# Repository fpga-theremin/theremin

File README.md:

# FPGA based theremin

Open source digital FPGA based theremin project.

Hardware design and build instructions can be found on [FPGA Theremin Project Page](https://fpga-theremin.github.io/theremin/)

[Theremin](https://en.wikipedia.org/wiki/Theremin) is an electronic musical instrument controlled without physical contact by the thereminist (performer).
It is named after the Westernized name of its Soviet inventor, Léon Theremin (Лев Термéн), who patented the device in 1928. 

FPGA Theremin project is attempt to build modern digital theremin with rich set of features.

## License 
FPGA Theremin is open source hardware and software project.

All hardware designed for this project 
is published under [TAPR Open Hardware License](https://www.tapr.org/TAPR_Open_Hardware_License_v1.0.txt)

All software (including both HDL and C/C++ code) 
is published under [GNU GENERAL PUBLIC LICENSE Version 2](https://www.gnu.org/licenses/old-licenses/gpl-2.0.txt)

## HDL sources

Modules are written in SystemVerilog.

Some of modules use Xilinx Series 7 specific hardware blocks.

HLD code for modules:

* [theremin_sensor](https://github.com/fpga-theremin/theremin/tree/master/fpga/ip_repo/theremin_ip/src/theremin_sensor) - double channel high precision frequency meter
* [encoders_board](https://github.com/fpga-theremin/theremin/tree/master/fpga/ip_repo/theremin_ip/src/encoders_board) - interfacing to 5 incremental encoders with buttons and one tact button
* [lcd_controller](https://github.com/fpga-theremin/theremin/tree/master/fpga/ip_repo/theremin_ip/src/lcd_controller) - LCD controller with RGB interface and DMA
* [audio_io](https://github.com/fpga-theremin/theremin/tree/master/fpga/ip_repo/theremin_ip/src/audio_io) - audio out 2 * stereo * 24bit * 48KHz I2S outputs and one stereo * 24bit * 48KHz I2S input
* [theremin_i2c](https://github.com/fpga-theremin/theremin/tree/master/fpga/ip_repo/theremin_ip/src/theremin_i2c) - I2C support
* [theremin_io](https://github.com/fpga-theremin/theremin/tree/master/fpga/ip_repo/theremin_ip/src/theremin_io) - Top Level Module combining all theremin peripherials

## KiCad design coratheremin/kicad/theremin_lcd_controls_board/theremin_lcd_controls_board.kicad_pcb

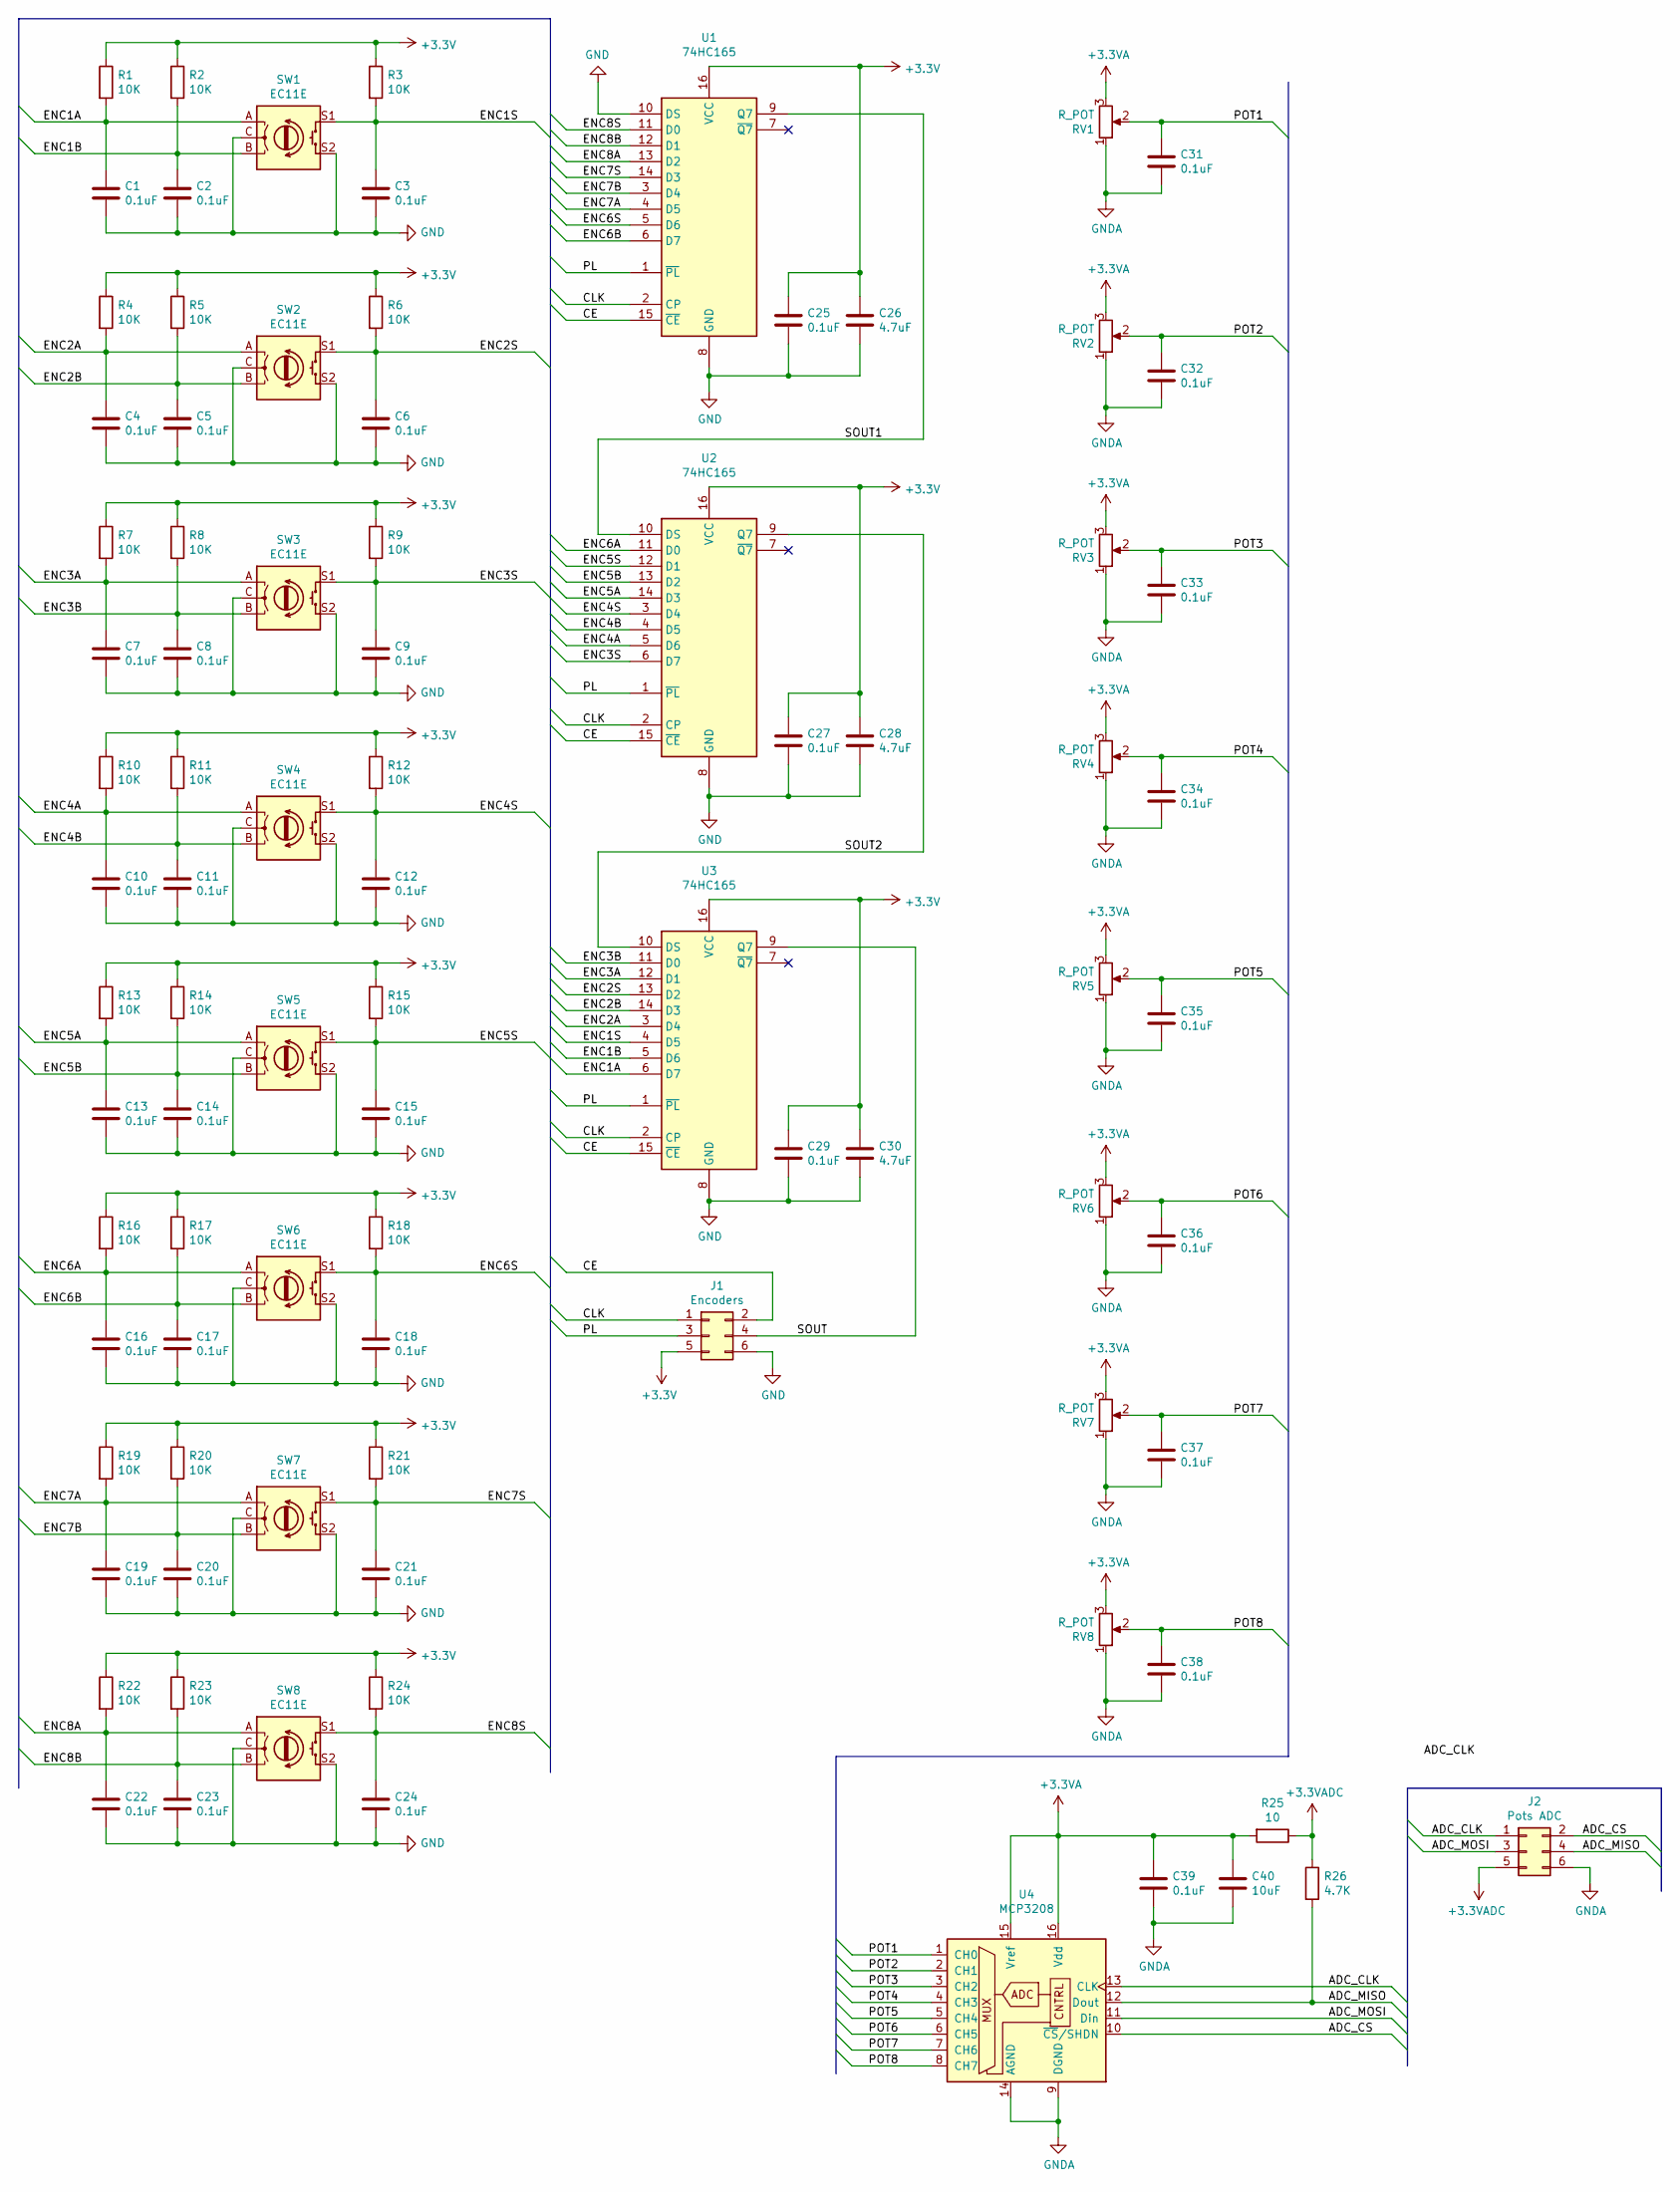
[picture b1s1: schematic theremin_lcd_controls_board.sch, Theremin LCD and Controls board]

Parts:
C1, C2, C3, C4, C5, C6, C7, C8, C9, C10, C11, C12, C13, C14, C15, C16, C17, C18, C19, C20, C21, C22, C23, C24, C25, C27, C29, C31, C32, C33, C34, C35, C36, C37, C38, C39: 0.1uF; C_0805_2012Metric
C26, C28, C30: 4.7uF; C_0805_2012Metric
C40: 10uF; C_0805_2012Metric
J1: Encoders; IDC-Header_2x03_P2.54mm_Vertical
J2: Pots ADC; IDC-Header_2x03_P2.54mm_Vertical
R1, R2, R3, R4, R5, R6, R7, R8, R9, R10, R11, R12, R13, R14, R15, R16, R17, R18, R19, R20, R21, R22, R23, R24: 10K; R_0805_2012Metric
R25: 10; R_0805_2012Metric
R26: 4.7K; R_0805_2012Metric
RV1, RV2, RV3, RV4, RV5, RV6, RV7, RV8: R_POT; Potentiometer_TT_P0915N
SW1, SW2, SW3, SW4, SW5, SW6, SW7, SW8: EC11E; RotaryEncoder_Alps_EC11E-Switch_Vertical_H20mm
U1, U2, U3: 74HC165; SO-16_3.9x9.9mm_P1.27mm
U4: MCP3208; SOIC-16_3.9x9.9mm_P1.27mm

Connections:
+3.3VA: C39.1, C40.1, R25.2, RV1.3, RV2.3, RV3.3, RV4.3, RV5.3, RV6.3, RV7.3, RV8.3, U4.15 (Vref), U4.16 (Vdd)
+3.3VADC: J2.5, R25.1, R26.1
+3V3: C25.1, C26.1, C27.1, C28.1, C29.1, C30.1, J1.5, R1.1, R2.1, R3.1, R4.1, R5.1, R6.1, R7.1, R8.1, R9.1, R10.1, R11.1, R12.1, R13.1, R14.1, R15.1, R16.1, R17.1, R18.1, R19.1, R20.1, R21.1, R22.1, R23.1, R24.1, U1.16 (VCC), U2.16 (VCC), U3.16 (VCC)
/ADC_CLK: J2.1, U4.13 (CLK)
/ADC_CS: J2.2, U4.10 (~CS~/SHDN)
/ADC_MISO: J2.4, R26.2, U4.12 (Dout)
/ADC_MOSI: J2.3, U4.11 (Din)
/CE: J1.2, U1.15 (~CE), U2.15 (~CE), U3.15 (~CE)
/CLK: J1.1, U1.2 (CP), U2.2 (CP), U3.2 (CP)
/ENC1A: C1.1, R1.2, SW1.A, U3.6 (D7)
/ENC1B: C2.1, R2.2, SW1.B, U3.5 (D6)
/ENC1S: C3.1, R3.2, SW1.S1, U3.4 (D5)
/ENC2A: C4.1, R4.2, SW2.A, U3.3 (D4)
/ENC2B: C5.1, R5.2, SW2.B, U3.14 (D3)
/ENC2S: C6.1, R6.2, SW2.S1, U3.13 (D2)
/ENC3A: C7.1, R7.2, SW3.A, U3.12 (D1)
/ENC3B: C8.1, R8.2, SW3.B, U3.11 (D0)
/ENC3S: C9.1, R9.2, SW3.S1, U2.6 (D7)
/ENC4A: C10.1, R10.2, SW4.A, U2.5 (D6)
/ENC4B: C11.1, R11.2, SW4.B, U2.4 (D5)
/ENC4S: C12.1, R12.2, SW4.S1, U2.3 (D4)
/ENC5A: C13.1, R13.2, SW5.A, U2.14 (D3)
/ENC5B: C14.1, R14.2, SW5.B, U2.13 (D2)
/ENC5S: C15.1, R15.2, SW5.S1, U2.12 (D1)
/ENC6A: C16.1, R16.2, SW6.A, U2.11 (D0)
/ENC6B: C17.1, R17.2, SW6.B, U1.6 (D7)
/ENC6S: C18.1, R18.2, SW6.S1, U1.5 (D6)
/ENC7A: C19.1, R19.2, SW7.A, U1.4 (D5)
/ENC7B: C20.1, R20.2, SW7.B, U1.3 (D4)
/ENC7S: C21.1, R21.2, SW7.S1, U1.14 (D3)
/ENC8A: C22.1, R22.2, SW8.A, U1.13 (D2)
/ENC8B: C23.1, R23.2, SW8.B, U1.12 (D1)
/ENC8S: C24.1, R24.2, SW8.S1, U1.11 (D0)
/PL: J1.3, U1.1 (~PL), U2.1 (~PL), U3.1 (~PL)
/POT1: C31.1, RV1.2, U4.1 (CH0)
/POT2: C32.1, RV2.2, U4.2 (CH1)
/POT3: C33.1, RV3.2, U4.3 (CH2)
/POT4: C34.1, RV4.2, U4.4 (CH3)
/POT5: C35.1, RV5.2, U4.5 (CH4)
/POT6: C36.1, RV6.2, U4.6 (CH5)
/POT7: C37.1, RV7.2, U4.7 (CH6)
/POT8: C38.1, RV8.2, U4.8 (CH7)
/SOUT: J1.4, U3.9 (Q7)
/SOUT1: U1.9 (Q7), U2.10 (DS)
/SOUT2: U2.9 (Q7), U3.10 (DS)
GND: C1.2, C2.2, C3.2, C4.2, C5.2, C6.2, C7.2, C8.2, C9.2, C10.2, C11.2, C12.2, C13.2, C14.2, C15.2, C16.2, C17.2, C18.2, C19.2, C20.2, C21.2, C22.2, C23.2, C24.2, C25.2, C26.2, C27.2, C28.2, C29.2, C30.2, J1.6, SW1.C, SW1.S2, SW2.C, SW2.S2, SW3.C, SW3.S2, SW4.C, SW4.S2, SW5.C, SW5.S2, SW6.C, SW6.S2, SW7.C, SW7.S2, SW8.C, SW8.S2, U1.8 (GND), U1.10 (DS), U2.8 (GND), U3.8 (GND)
GNDA: C31.2, C32.2, C33.2, C34.2, C35.2, C36.2, C37.2, C38.2, C39.2, C40.2, J2.6, RV1.1, RV2.1, RV3.1, RV4.1, RV5.1, RV6.1, RV7.1, RV8.1, U4.9 (DGND), U4.14 (AGND)

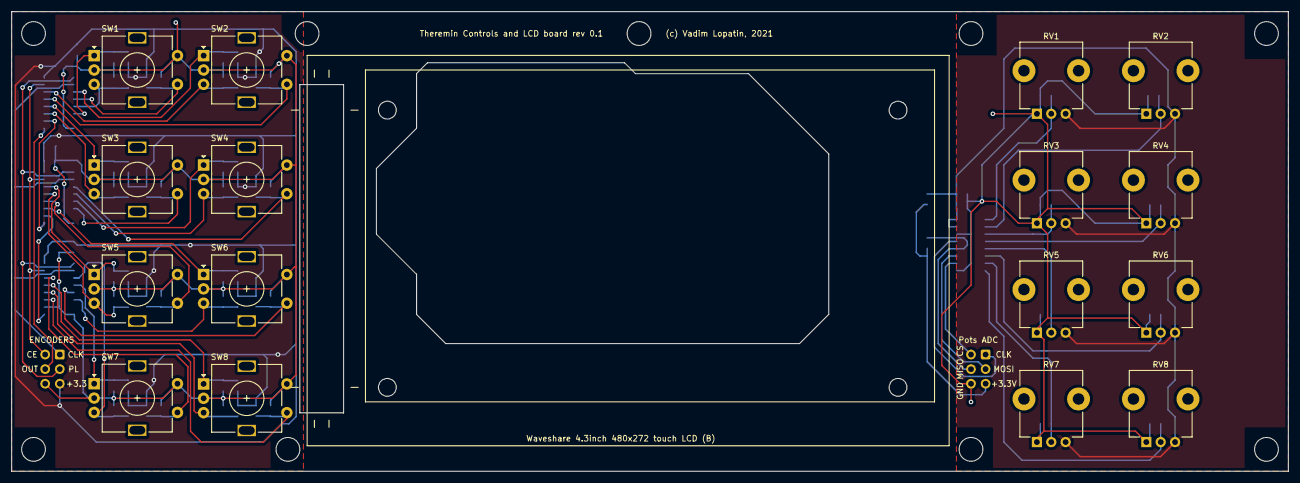
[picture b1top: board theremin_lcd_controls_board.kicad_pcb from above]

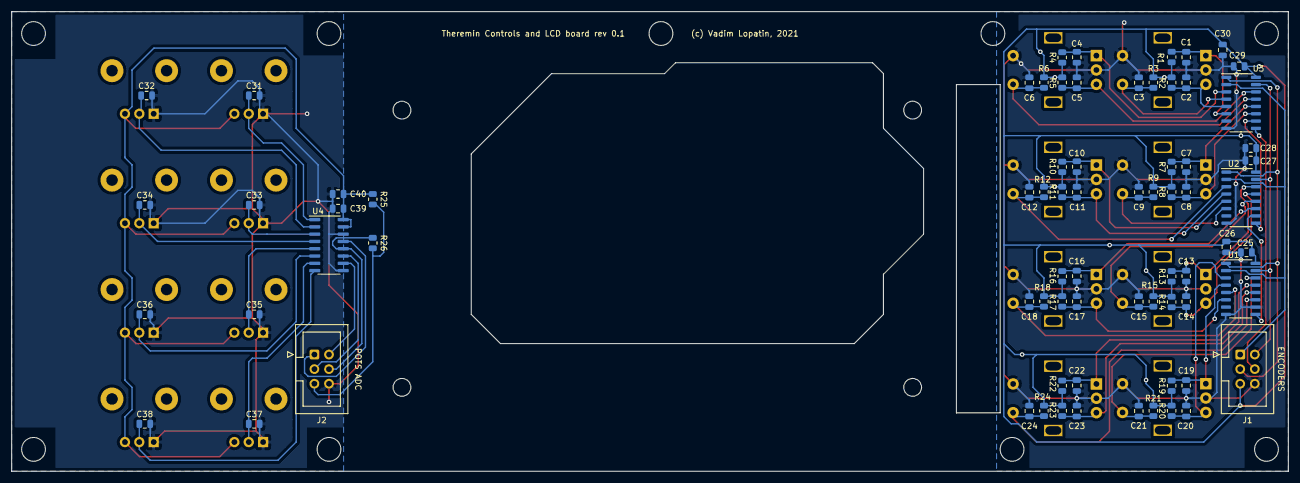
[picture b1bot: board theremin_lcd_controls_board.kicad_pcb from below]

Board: 2 copper layers, 222.2 x 80.0 mm, 88 parts (72 on the bottom side), 47 nets.

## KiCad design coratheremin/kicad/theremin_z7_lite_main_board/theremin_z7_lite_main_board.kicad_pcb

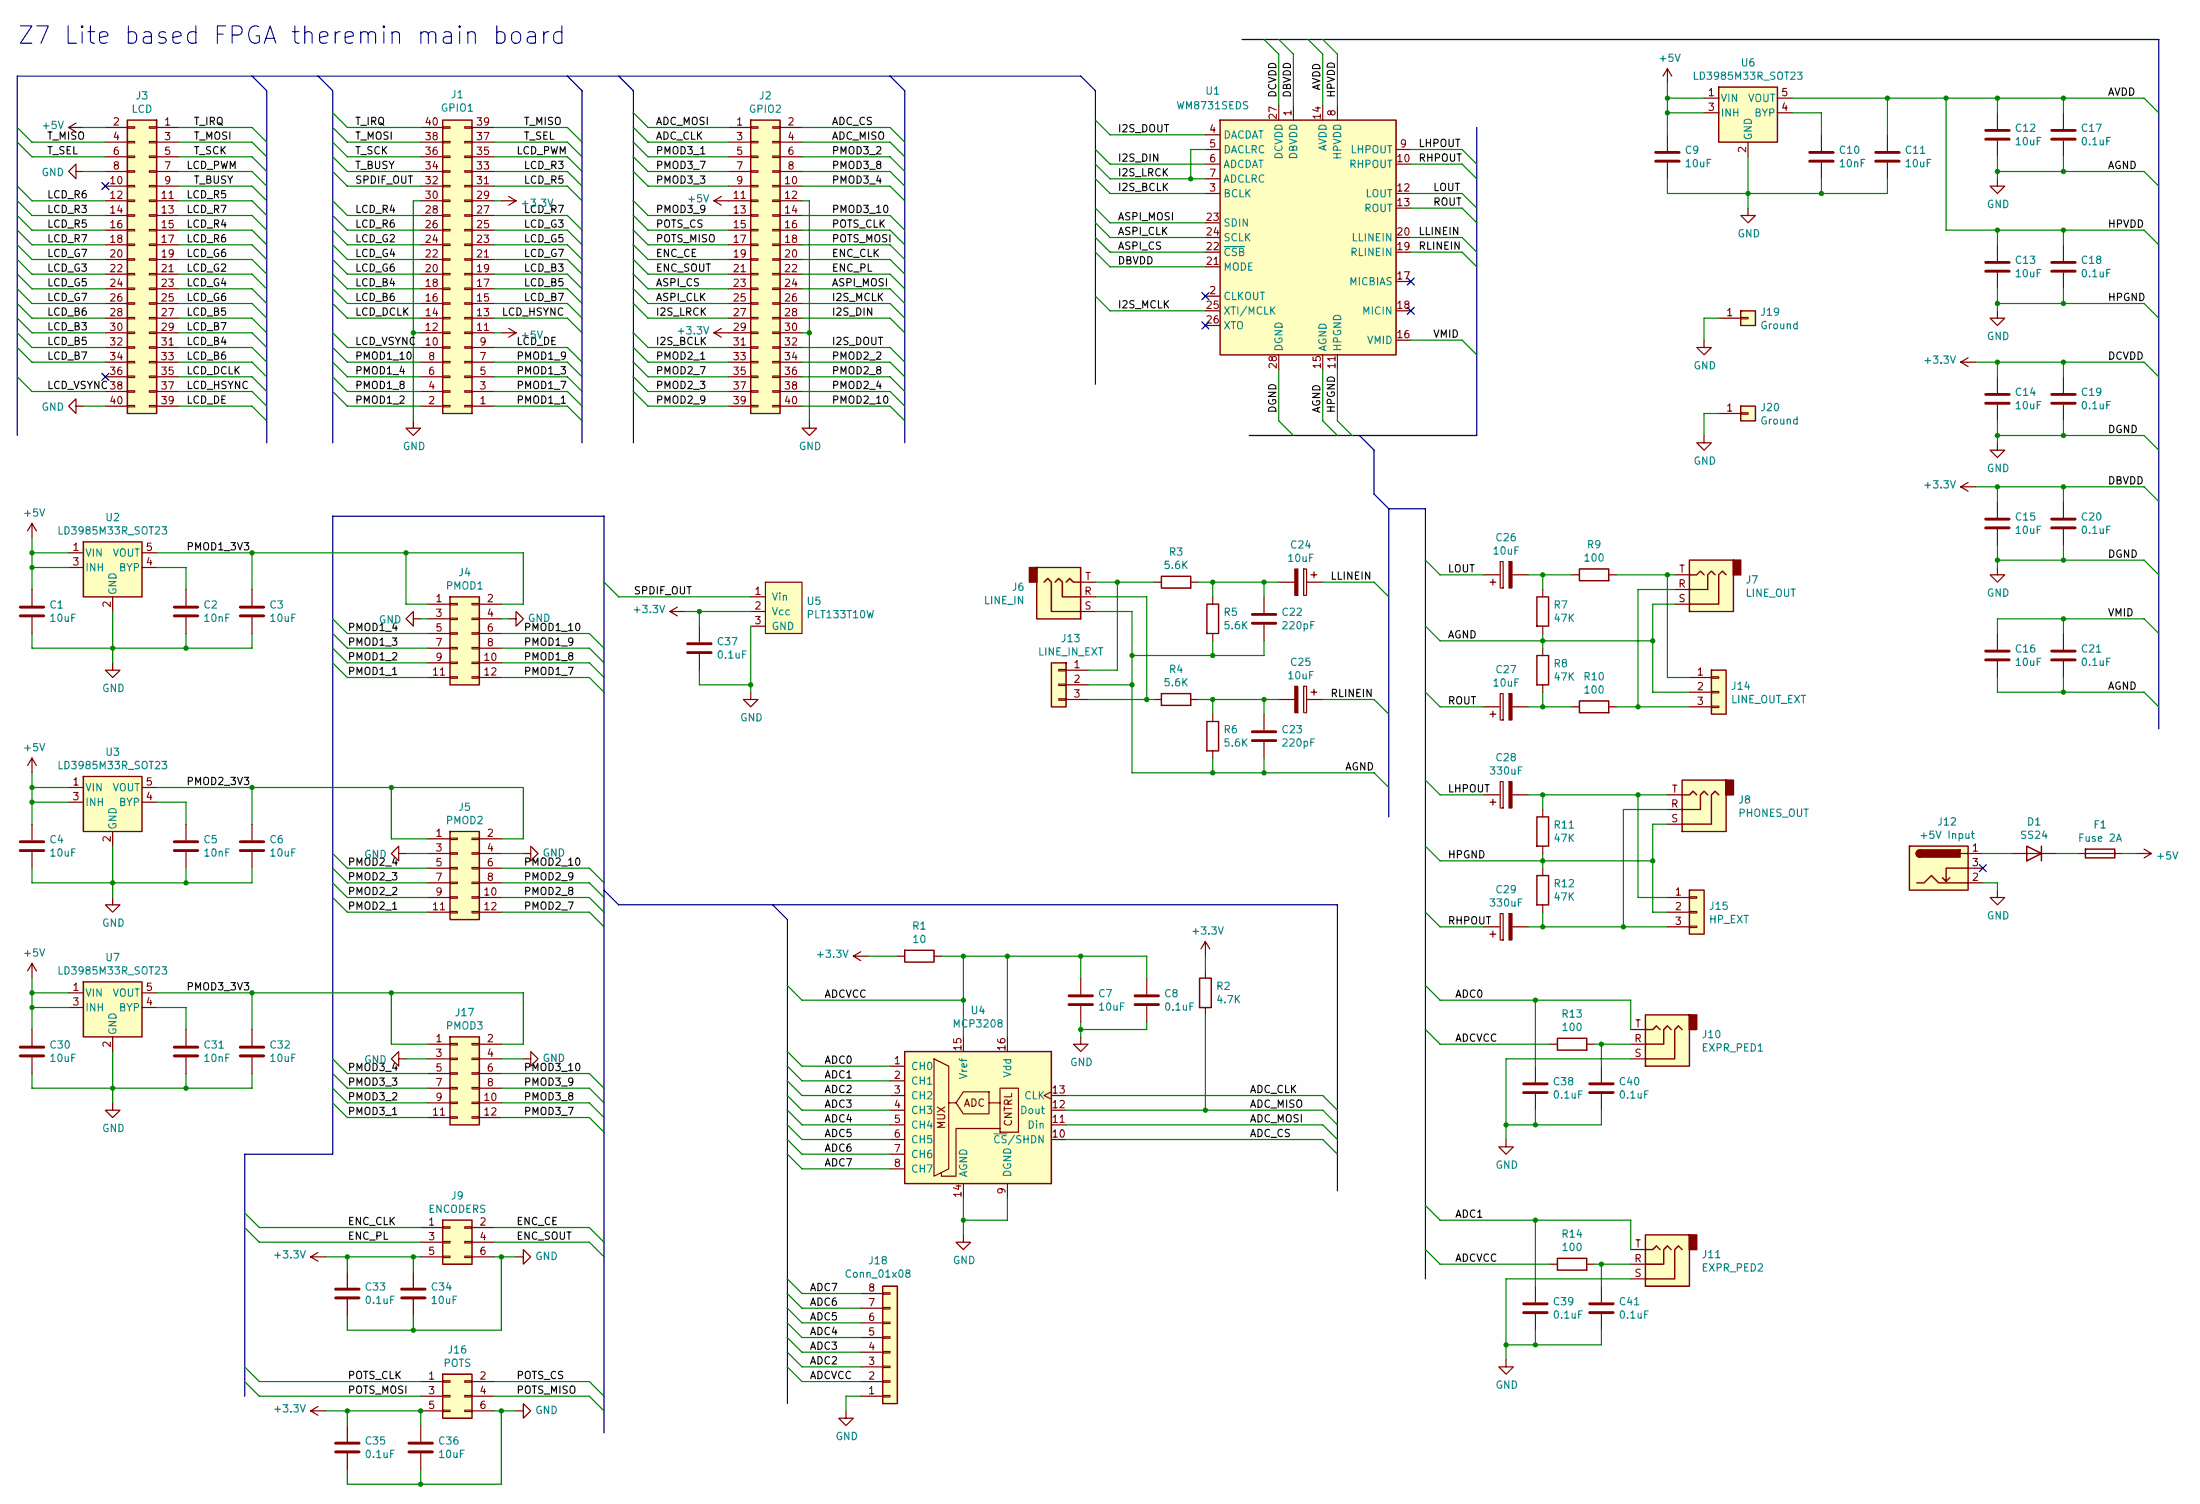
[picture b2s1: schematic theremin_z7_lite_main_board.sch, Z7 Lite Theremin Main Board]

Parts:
C1, C3, C4, C6, C7, C9, C11, C12, C13, C14, C15, C16, C30, C32, C34, C36: 10uF; C_0805_2012Metric
C2, C5, C10, C31: 10nF; C_0805_2012Metric
C8, C17, C18, C19, C20, C21, C33, C35, C37, C38, C39, C40, C41: 0.1uF; C_0805_2012Metric
C22, C23: 220pF; C_0805_2012Metric
C24, C25, C26, C27: 10uF; CP_Radial_D5.0mm_P2.00mm
C28, C29: 330uF; CP_Radial_D6.3mm_P2.50mm
D1: SS24; D_SMB
F1: Fuse 2A; Fuse_1206_3216Metric
J1: GPIO1; PinSocket_2x20_P2.54mm_Vertical
J2: GPIO2; PinSocket_2x20_P2.54mm_Vertical
J3: LCD; IDC-Header_2x20_P2.54mm_Vertical
J4: PMOD1; PinSocket_2x06_P2.54mm_Horizontal
J5: PMOD2; PinSocket_2x06_P2.54mm_Horizontal
J6: LINE_IN; Jack_6.35mm_ST_008G_04
J7: LINE_OUT; Jack_6.35mm_ST_008G_04
J8: PHONES_OUT; Jack_3.5mm_CUI_SJ1-3533NG_Horizontal
J9: ENCODERS; IDC-Header_2x03_P2.54mm_Vertical
J10: EXPR_PED1; Jack_6.35mm_ST_008G_04
J11: EXPR_PED2; Jack_6.35mm_ST_008G_04
J12: +5V Input; BarrelJack_Wuerth_6941xx301002
J13: LINE_IN_EXT; PinHeader_1x03_P2.54mm_Vertical
J14: LINE_OUT_EXT; PinHeader_1x03_P2.54mm_Vertical
J15: HP_EXT; PinHeader_1x03_P2.54mm_Vertical
J16: POTS; IDC-Header_2x03_P2.54mm_Vertical
J17: PMOD3; PinSocket_2x06_P2.54mm_Horizontal
J18: Conn_01x08; PinHeader_1x08_P2.54mm_Vertical
J19, J20: Ground; PinHeader_1x01_P2.54mm_Vertical
R1: 10; R_0805_2012Metric
R2: 4.7K; R_0805_2012Metric
R3, R4, R5, R6: 5.6K; R_0805_2012Metric
R7, R8, R11, R12: 47K; R_0805_2012Metric
R9, R10, R13, R14: 100; R_0805_2012Metric
U1: WM8731SEDS; SSOP-28_5.3x10.2mm_P0.65mm
U2, U3, U6, U7: LD3985M33R_SOT23; SOT-23-5
U4: MCP3208; SOIC-16_3.9x9.9mm_P1.27mm
U5: PLT133T10W

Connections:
+3V3: C14.1, C15.1, C19.1, C20.1, C33.1, C34.1, C35.1, C36.1, C37.1, J1.29, J2.29, J9.5, J16.5, R1.2, R2.1, U1.1 (DBVDD), U1.21 (MODE), U1.27 (DCVDD), U5.2 (Vcc)
+5V: C1.1, C4.1, C9.1, C30.1, F1.1, J1.11, J2.11, J3.2, U2.1 (VIN), U2.3 (INH), U3.1 (VIN), U3.3 (INH), U6.1 (VIN), U6.3 (INH), U7.1 (VIN), U7.3 (INH)
/ADC0: C38.1, J10.T, U4.1 (CH0)
/ADC1: C39.1, J11.T, U4.2 (CH1)
/ADC2: J18.3, U4.3 (CH2)
/ADC3: J18.4, U4.4 (CH3)
/ADC4: J18.5, U4.5 (CH4)
/ADC5: J18.6, U4.6 (CH5)
/ADC6: J18.7, U4.7 (CH6)
/ADC7: J18.8, U4.8 (CH7)
/ADCVCC: C7.1, C8.1, J18.2, R1.1, R13.1, R14.1, U4.15 (Vref), U4.16 (Vdd)
/ADC_CLK: J2.3, U4.13 (CLK)
/ADC_CS: J2.2, U4.10 (~CS~/SHDN)
/ADC_MISO: J2.4, R2.2, U4.12 (Dout)
/ADC_MOSI: J2.1, U4.11 (Din)
/ASPI_CLK: J2.25, U1.24 (SCLK)
/ASPI_CS: J2.23, U1.22 (~CSB)
/ASPI_MOSI: J2.24, U1.23 (SDIN)
/AVDD: C11.1, C12.1, C13.1, C17.1, C18.1, U1.8 (HPVDD), U1.14 (AVDD), U6.5 (VOUT)
/ENC_CE: J2.19, J9.2
/ENC_CLK: J2.20, J9.1
/ENC_PL: J2.22, J9.3
/ENC_SOUT: J2.21, J9.4
/I2S_BCLK: J2.31, U1.3 (BCLK)
/I2S_DIN: J2.28, U1.6 (ADCDAT)
/I2S_DOUT: J2.32, U1.4 (DACDAT)
/I2S_LRCK: J2.27, U1.5 (DACLRC), U1.7 (ADCLRC)
/I2S_MCLK: J2.26, U1.25 (XTI/MCLK)
/LCD_B3: J1.19, J3.30
/LCD_B4: J1.18, J3.31
/LCD_B5: J1.17, J3.27, J3.32
/LCD_B6: J1.16, J3.28, J3.33
/LCD_B7: J1.15, J3.29, J3.34
/LCD_DCLK: J1.14, J3.35
/LCD_DE: J1.9, J3.39
/LCD_G2: J1.24, J3.21
/LCD_G3: J1.25, J3.22
/LCD_G4: J1.22, J3.23
/LCD_G5: J1.23, J3.24
/LCD_G6: J1.20, J3.19, J3.25
/LCD_G7: J1.21, J3.20, J3.26
/LCD_HSYNC: J1.13, J3.37
/LCD_PWM: J1.35, J3.7
/LCD_R3: J1.33, J3.14
/LCD_R4: J1.28, J3.15
/LCD_R5: J1.31, J3.11, J3.16
/LCD_R6: J1.26, J3.12, J3.17
/LCD_R7: J1.27, J3.13, J3.18
/LCD_VSYNC: J1.10, J3.38
/LHPOUT: C28.1, U1.9 (LHPOUT)
/LLINEIN: C24.1, U1.20 (LLINEIN)
/LOUT: C26.1, U1.12 (LOUT)
/PMOD1_1: J1.1, J4.11
/PMOD1_2: J1.2, J4.9
/PMOD1_3: J1.5, J4.7
/PMOD1_3V3: C3.1, J4.1, J4.2, U2.5 (VOUT)
/PMOD1_4: J1.6, J4.5
/PMOD1_7: J1.3, J4.12
/PMOD1_8: J1.4, J4.10
/PMOD1_9: J1.7, J4.8
/PMOD1_10: J1.8, J4.6
/PMOD2_1: J2.33, J5.11
/PMOD2_2: J2.34, J5.9
/PMOD2_3: J2.37, J5.7
/PMOD2_3V3: C6.1, J5.1, J5.2, U3.5 (VOUT)
/PMOD2_4: J2.38, J5.5
/PMOD2_7: J2.35, J5.12
/PMOD2_8: J2.36, J5.10
/PMOD2_9: J2.39, J5.8
/PMOD2_10: J2.40, J5.6
/PMOD3_1: J2.5, J17.11
/PMOD3_2: J2.6, J17.9
/PMOD3_3: J2.9, J17.7
/PMOD3_3V3: C32.1, J17.1, J17.2, U7.5 (VOUT)
/PMOD3_4: J2.10, J17.5
/PMOD3_7: J2.7, J17.12
/PMOD3_8: J2.8, J17.10
/PMOD3_9: J2.13, J17.8
/PMOD3_10: J2.14, J17.6
/POTS_CLK: J2.16, J16.1
/POTS_CS: J2.15, J16.2
/POTS_MISO: J2.17, J16.4
/POTS_MOSI: J2.18, J16.3
/RHPOUT: C29.1, U1.10 (RHPOUT)
/RLINEIN: C25.1, U1.19 (RLINEIN)
/ROUT: C27.1, U1.13 (ROUT)
/SPDIF_OUT: J1.32, U5.1 (Vin)
/T_BUSY: J1.34, J3.9
/T_IRQ: J1.40, J3.1
/T_MISO: J1.39, J3.4
/T_MOSI: J1.38, J3.3
/T_SCK: J1.36, J3.5
/T_SEL: J1.37, J3.6
/VMID: C16.1, C21.1, U1.16 (VMID)
GND: C1.2, C2.2, C3.2, C4.2, C5.2, C6.2, C7.2, C8.2, C9.2, C10.2, C11.2, C12.2, C13.2, C14.2, C15.2, C16.2, C17.2, C18.2, C19.2, C20.2, C21.2, C22.2, C23.2, C30.2, C31.2, C32.2, C33.2, C34.2, C35.2, C36.2, C37.2, C38.2, C39.2, C40.2, C41.2, J1.12, J1.30, J2.12, J2.30, J3.8, J3.40, J4.3, J4.4, J5.3, J5.4, J6.S, J7.S, J8.S, J9.6, J10.S, J11.S, J12.2, J13.2, J14.2, J15.2, J16.6, J17.3, J17.4, J18.1, J19.1, J20.1, R5.2, R6.2, R7.2, R8.1, R11.2, R12.1, U1.11 (HPGND), U1.15 (AGND), U1.28 (DGND), U2.2 (GND), U3.2 (GND), U4.9 (DGND), U4.14 (AGND), U5.3 (GND), U6.2 (GND), U7.2 (GND)
unnamed: C2.1, U2.4 (BYP)
unnamed: C5.1, U3.4 (BYP)
unnamed: C10.1, U6.4 (BYP)
unnamed: C22.1, C24.2, R3.2, R5.1
unnamed: C23.1, C25.2, R4.2, R6.1
unnamed: C26.2, R7.1, R9.1
unnamed: C27.2, R8.2, R10.1
unnamed: C28.2, J8.T, J15.1, R11.1
unnamed: C29.2, J8.R, J15.3, R12.2
unnamed: C31.1, U7.4 (BYP)
unnamed: C40.1, J10.R, R13.2
unnamed: C41.1, J11.R, R14.2
unnamed: D1.1 (K), F1.2
unnamed: D1.2 (A), J12.1
unnamed: J6.T, J13.1, R3.1
unnamed: J6.R, J13.3, R4.1
unnamed: J7.T, J14.1, R9.2
unnamed: J7.R, J14.3, R10.2

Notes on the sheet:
Z7 Lite based FPGA theremin main board

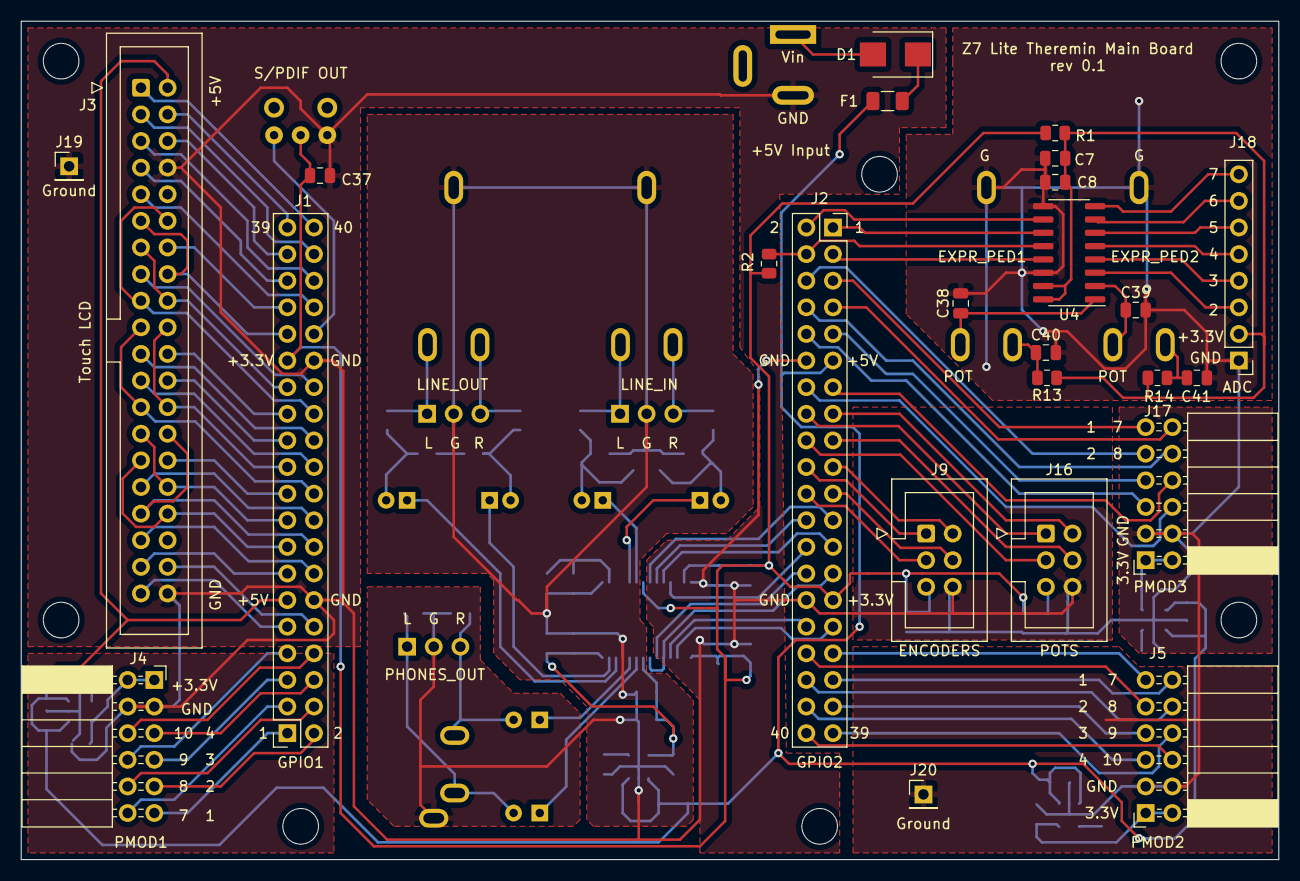
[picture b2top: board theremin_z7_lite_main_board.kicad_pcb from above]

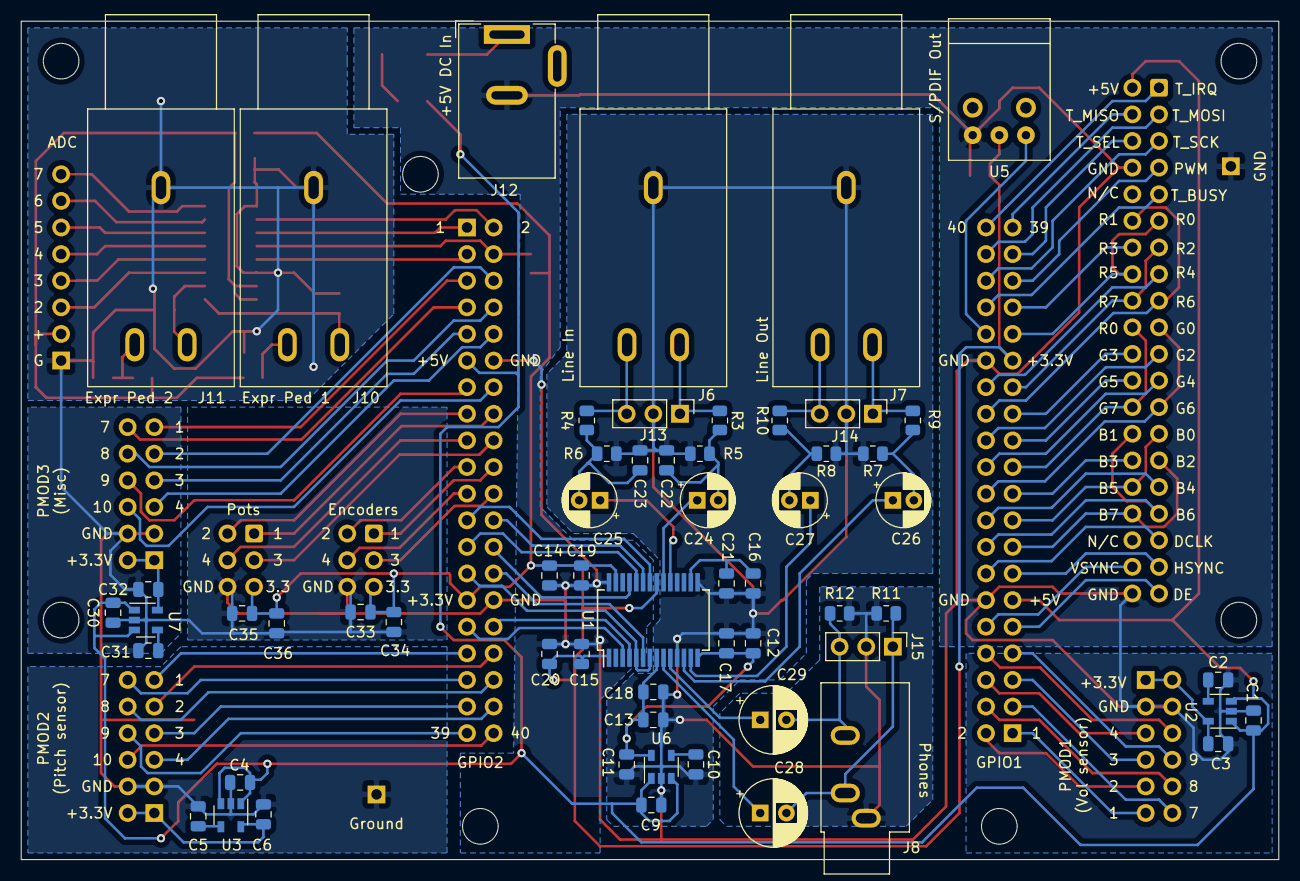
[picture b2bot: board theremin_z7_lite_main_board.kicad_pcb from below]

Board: 2 copper layers, 120.0 x 80.0 mm, 84 parts (59 on the bottom side), 113 nets.

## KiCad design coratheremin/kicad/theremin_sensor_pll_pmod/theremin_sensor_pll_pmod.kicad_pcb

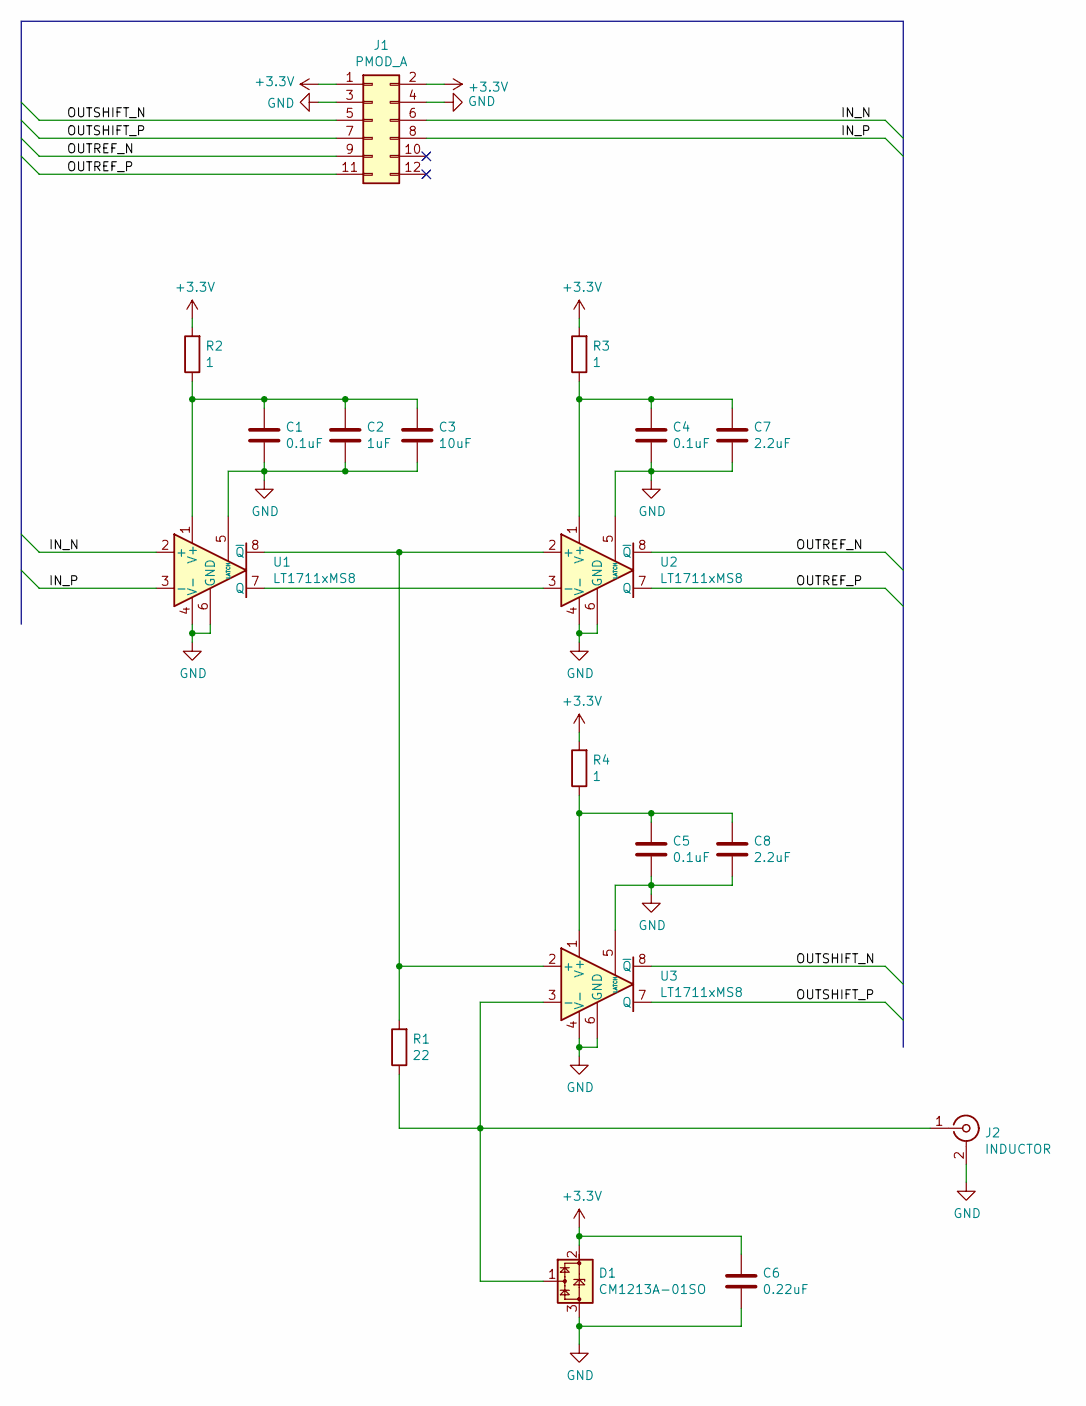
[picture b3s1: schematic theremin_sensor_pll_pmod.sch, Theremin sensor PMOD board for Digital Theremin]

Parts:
C1, C4, C5: 0.1uF; C_0805_2012Metric_Pad1.18x1.45mm_HandSolder
C2: 1uF; C_0805_2012Metric_Pad1.18x1.45mm_HandSolder
C3: 10uF; C_0805_2012Metric_Pad1.18x1.45mm_HandSolder
C6: 0.22uF; C_0805_2012Metric_Pad1.18x1.45mm_HandSolder
C7, C8: 2.2uF; C_0805_2012Metric_Pad1.18x1.45mm_HandSolder
D1: CM1213A-01SO; SOT-23
J1: PMOD_A; PinHeader_2x06_P2.54mm_Horizontal
J2: INDUCTOR; SMA_Wurth_60312002114503_Vertical
R1: 22; R_0805_2012Metric
R2, R3, R4: 1; R_0805_2012Metric
U1, U2, U3: LT1711xMS8; MSOP-8_3x3mm_P0.65mm

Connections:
+3V3: C6.1, D1.2 (VP), J1.1, J1.2, R2.2, R3.2, R4.2
/IN_N: J1.6, U1.2 (+)
/IN_P: J1.8, U1.3 (-)
/OUTREF_N: J1.9, U2.8 (~Q)
/OUTREF_P: J1.11, U2.7 (Q)
/OUTSHIFT_N: J1.5, U3.8 (~Q)
/OUTSHIFT_P: J1.7, U3.7 (Q)
GND: C1.2, C2.2, C3.2, C4.2, C5.2, C6.2, C7.2, C8.2, D1.3 (VN), J1.3, J1.4, J2.2 (Ext), U1.4 (V-), U1.5 (LATCH), U1.6 (GND), U2.4 (V-), U2.5 (LATCH), U2.6 (GND), U3.4 (V-), U3.5 (LATCH), U3.6 (GND)
unnamed: C1.1, C2.1, C3.1, R2.1, U1.1 (V+)
unnamed: C4.1, C7.1, R3.1, U2.1 (V+)
unnamed: C5.1, C8.1, R4.1, U3.1 (V+)
unnamed: D1.1 (CH1), J2.1 (In), R1.1, U3.3 (-)
unnamed: R1.2, U1.8 (~Q), U2.2 (+), U3.2 (+)
unnamed: U1.7 (Q), U2.3 (-)

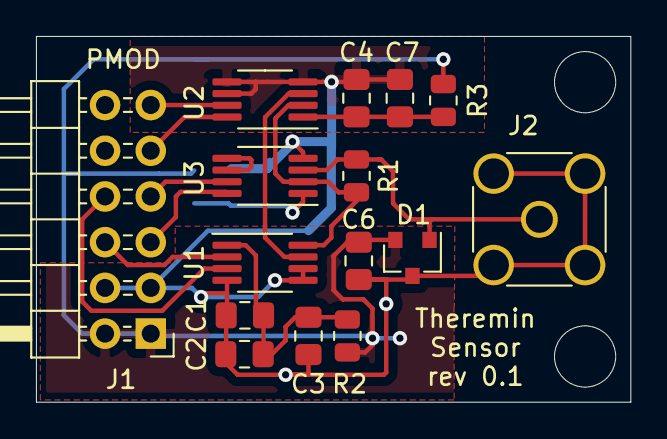
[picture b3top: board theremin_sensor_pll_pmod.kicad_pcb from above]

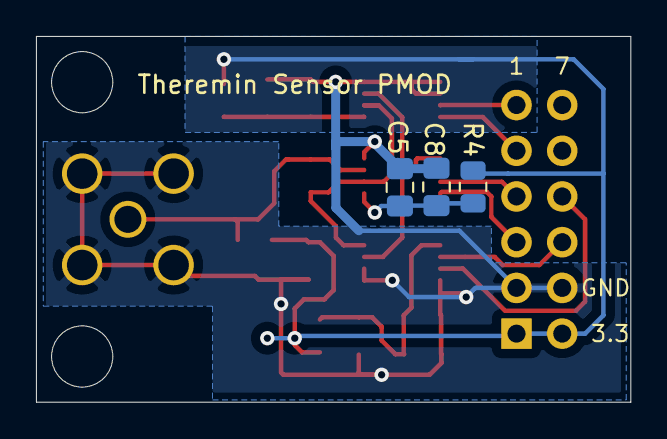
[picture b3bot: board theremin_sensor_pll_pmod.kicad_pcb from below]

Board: 2 copper layers, 33.0 x 20.3 mm, 18 parts (3 on the bottom side), 14 nets.

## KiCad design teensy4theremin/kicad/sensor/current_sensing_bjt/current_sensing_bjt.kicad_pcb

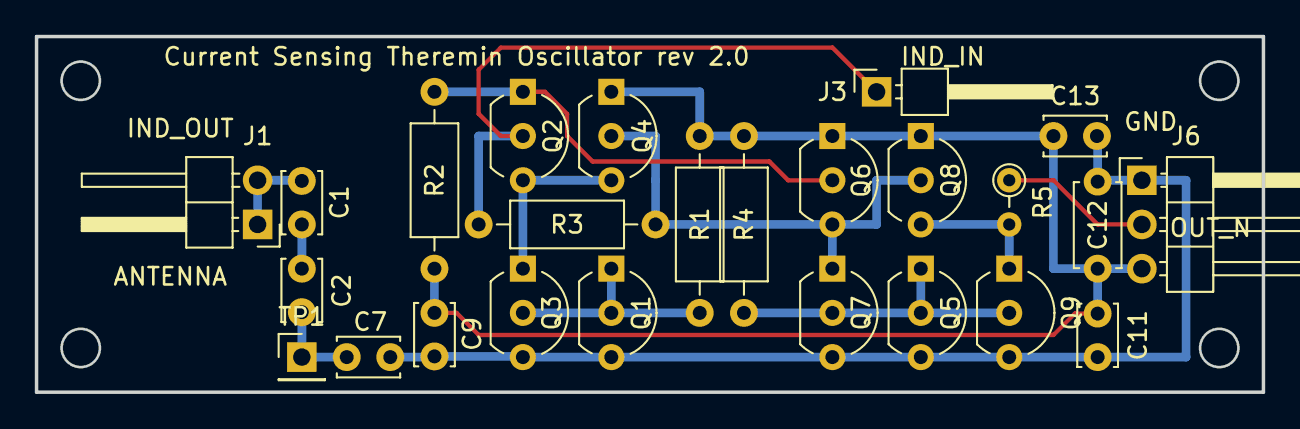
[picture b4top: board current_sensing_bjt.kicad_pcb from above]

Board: 2 copper layers, 70.5 x 20.4 mm, 25 parts (0 on the bottom side), 13 nets.

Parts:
C1, C2: 1pF; C_Disc_D3.4mm_W2.1mm_P2.50mm
C7: 1000pF; C_Disc_D3.4mm_W2.1mm_P2.50mm
C9, C11, C13: 0.1uF; C_Disc_D3.4mm_W2.1mm_P2.50mm
C12: 10uF; C_Disc_D4.7mm_W2.5mm_P5.00mm
J1: ANTENNA; PinHeader_1x02_P2.54mm_Horizontal
J3: INDUCTOR_IN; PinHeader_1x01_P2.54mm_Horizontal
J6: OSC; PinHeader_1x03_P2.54mm_Horizontal
Q1, Q2, Q3, Q4, Q5, Q6, Q7, Q8, Q9: BC549; TO-92_Inline_Wide
R1, R2: 4.7K; R_Axial_DIN0207_L6.3mm_D2.5mm_P10.16mm_Horizontal
R3: 47; R_Axial_DIN0207_L6.3mm_D2.5mm_P10.16mm_Horizontal
R4: 680; R_Axial_DIN0207_L6.3mm_D2.5mm_P10.16mm_Horizontal
R5: 100; R_Axial_DIN0204_L3.6mm_D1.6mm_P2.54mm_Vertical
TP1: Antenna Voltage Swing; PinHeader_1x01_P2.54mm_Vertical

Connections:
/OUT: J6.2, R5.1
GND: C7.2, C9.2, C11.2, C12.2, C13.2, J6.1, Q1.3, Q3.3, Q5.3, Q7.3, Q9.3
unnamed: C1.1, C2.2
unnamed: C1.2, J1.1, J1.2
unnamed: C2.1, C7.1, TP1.1
unnamed: J3.1, Q2.2, R3.2
unnamed: Q1.1, Q1.2, Q3.2, R1.2
unnamed: Q2.1, Q6.2, R2.2
unnamed: Q2.3, Q3.1, Q4.3
unnamed: Q4.2, Q6.3, Q7.1, Q8.2, R3.1
unnamed: Q5.1, Q5.2, Q7.2, Q9.2, R4.2
unnamed: Q8.3, Q9.1, R5.2
VCC: C9.1, C11.1, C12.1, C13.1, J6.3, Q4.1, Q6.1, Q8.1, R1.1, R2.1, R4.1
